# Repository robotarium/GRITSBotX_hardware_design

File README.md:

# GRITSBotX_hardware_design
Documentation relative to the GritsbotX robot circuit board, chassis, and assembly instructions.

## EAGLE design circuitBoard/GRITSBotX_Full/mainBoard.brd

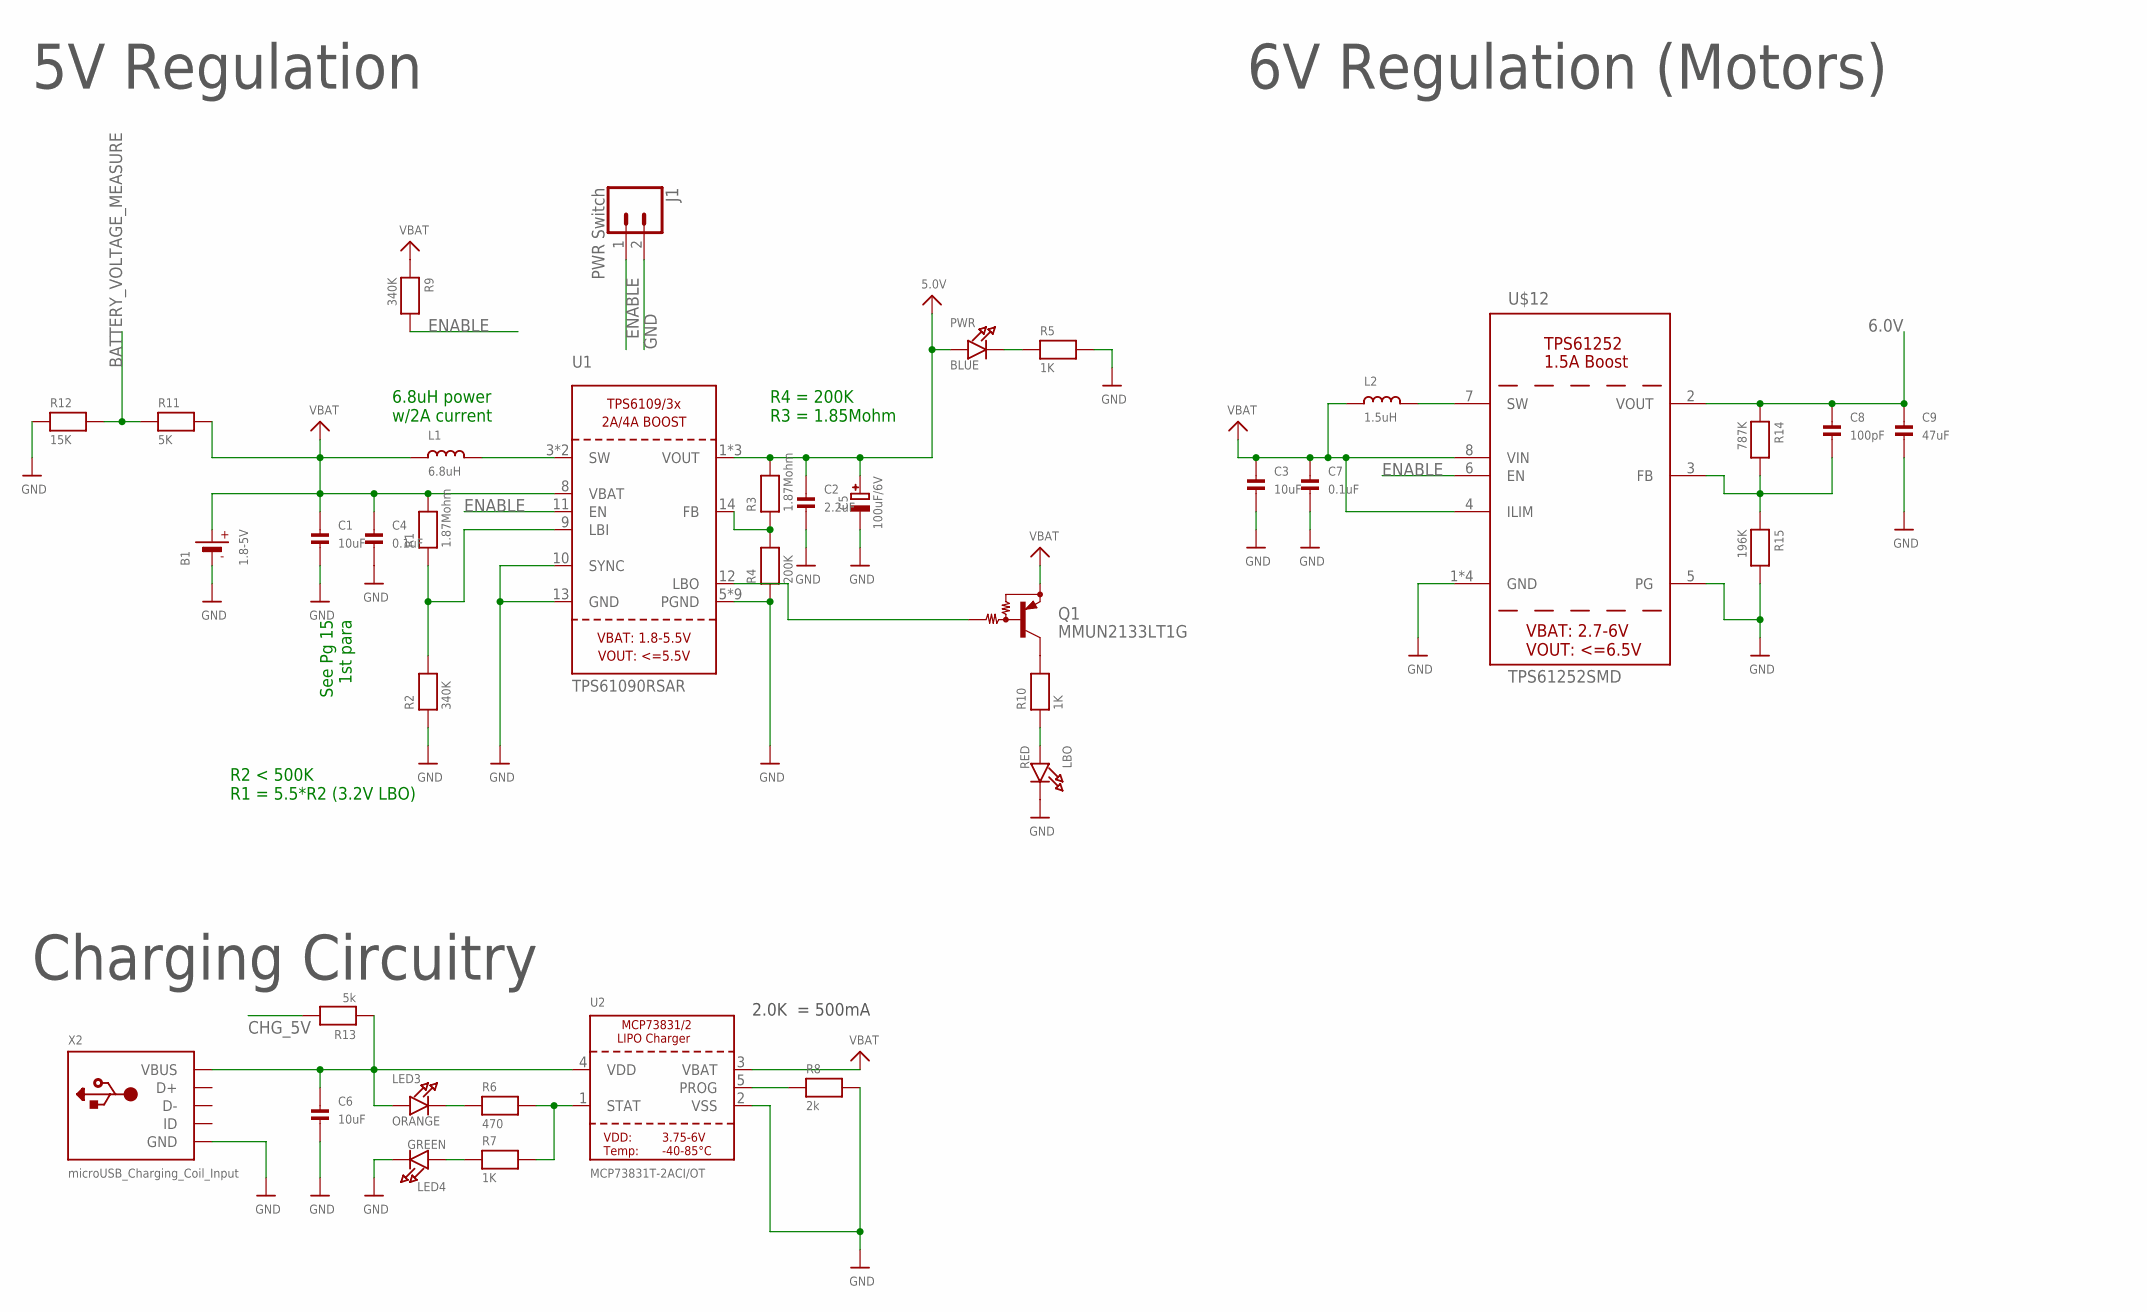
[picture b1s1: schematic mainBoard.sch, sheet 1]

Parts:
B1: 1.8-5V; JSTPH2
C1, C3, C6: 10uF; 0603
C2: 2.2uF; 0603
C4, C7: 0.1uF; 0805
C5: 100uF/6V; EIA3528-21/B-R
C8: 100pF; 0603
C9: 47uF; 1206
J1: PWR Switch; 1X02
L1: 6.8uH; VISHAY_IHLP2525CZER6R8M01
L2: 1.5uH; MURATA_DFE252012P-1R5M=P2
LBO: RED; CHIPLED_0805_NOOUTLINE
LED3: ORANGE; CHIPLED_0805_NOOUTLINE
LED4: GREEN; CHIPLED_0805_NOOUTLINE
PWR: BLUE; CHIPLED_0805_NOOUTLINE
Q1: MMUN2133LT1G; SC59-BEC
R1, R3: 1.87Mohm; 0805
R2, R9: 340K; 0805
R4: 200K; 0805
R5, R7, R10: 1K; 0805
R6: 470; 0805
R8: 2k; 0805
R11: 5K; 0805
R12: 15K; 0805
R13: 5k; 0805
R14: 787K; 0805
R15: 196K; 0805
U1: TPS61090RSAR; PVQFN-16
U2: MCP73831T-2ACI/OT; SOT23-5
U$12: TPS61252SMD; TPS61252
X2: microUSB_Charging_Coil_Input; 4UCONN_20329

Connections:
5.0V: C2.1, C5.+, PWR.A, R3.2, U1.1 (VOUT), U1.15 (VOUT), U1.16 (VOUT); also elsewhere on the board
6.0V: C8.1, C9.1, R14.1, U$12.2 (VOUT); also elsewhere on the board
BATTERY_VOLTAGE_MEASURE: R11.1, R12.2; also elsewhere on the board
CHARGING_BOOL_5V: C6.1, LED3.A, R13.1, U2.4 (VDD), X2.VBUS
CHG_5V: R13.2; also elsewhere on the board
ENABLE: J1.1, R9.2, U1.11 (EN), U$12.6 (EN)
GND: B1.1 (-), C1.2, C2.2, C3.2, C4.2, C5.-, C6.2, C7.2, C9.2, J1.2, LBO.C, LED4.C, R2.1, R4.1, R5.2, R8.2, R12.1, R15.2, U1.5 (PGND), U1.6 (PGND), U1.7 (PGND), U1.10 (SYNC), U1.13 (GND), U1.P$18 (PGND), U1.P$19 (PGND), U1.P$20 (PGND), U1.P$21 (PGND), U1.P$22 (PGND), U1.THERMAL (PGND), U2.2 (VSS), U$12.1 (GND), U$12.5 (PG), U$12.P$2_GND (GND), U$12.P$3_GND (GND), U$12.THERMAL_GND (GND), X2.BASE@1 (GND), X2.BASE@2 (GND), X2.GND, X2.SPRT@1 (GND), X2.SPRT@2 (GND), X2.SPRT@3 (GND), X2.SPRT@4 (GND); also elsewhere on the board
LBO: Q1.B, U1.12 (LBO)
unnamed: L1.P$2 (2), U1.3 (SW), U1.4 (SW)
unnamed: LBO.A, R10.1
unnamed: R1.1, R2.2, U1.9 (LBI)
unnamed: PWR.C, R5.1
unnamed: R3.1, R4.2, U1.14 (FB)
unnamed: LED3.C, R6.1
unnamed: R6.2, R7.2, U2.1 (STAT)
unnamed: R8.1, U2.5 (PROG)
unnamed: LED4.A, R7.1
unnamed: Q1.C, R10.2
unnamed: L2.P$2 (2), U$12.7 (SW)
unnamed: C8.2, R14.2, R15.1, U$12.3 (FB)
VBAT: B1.2 (+), C1.1, C3.1, C4.1, C7.1, L1.P$1 (1), L2.P$1 (1), Q1.E, R1.2, R9.1, R11.2, U1.8 (VBAT), U2.3 (VBAT), U$12.4 (ILIM), U$12.8 (VIN)

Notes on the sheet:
See Pg 15 1st para
6.8uH power w/2A current
R2 < 500K R1 = 5.5*R2 (3.2V LBO)
R4 = 200K R3 = 1.85Mohm
2.0K = 500mA
Charging Circuitry
5V Regulation
6V Regulation (Motors)

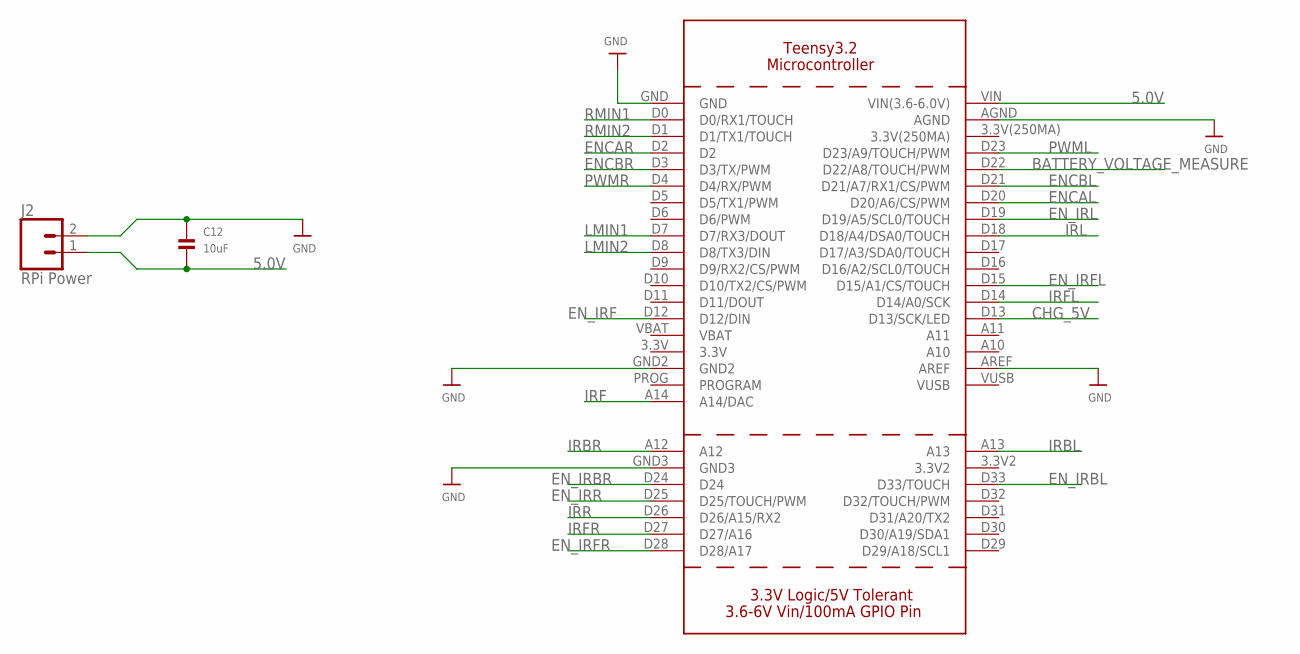
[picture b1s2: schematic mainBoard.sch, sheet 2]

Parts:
C12: 10uF; 0603
J2: RPi Power; 1X02
U$28: TEENSY3_2

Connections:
5.0V: C12.2, J2.1, U$28.VIN (VIN(3.6-6.0V)); also elsewhere on the board
BATTERY_VOLTAGE_MEASURE: U$28.D22 (D22/A8/TOUCH/PWM); also elsewhere on the board
CHG_5V: U$28.D13 (D13/SCK/LED); also elsewhere on the board
ENCAL: U$28.D20 (D20/A6/CS/PWM); also elsewhere on the board
ENCAR: U$28.D2; also elsewhere on the board
ENCBL: U$28.D21 (D21/A7/RX1/CS/PWM); also elsewhere on the board
ENCBR: U$28.D3 (D3/TX/PWM); also elsewhere on the board
EN_IRBL: U$28.D33 (D33/TOUCH); also elsewhere on the board
EN_IRBR: U$28.D24; also elsewhere on the board
EN_IRF: U$28.D12 (D12/DIN); also elsewhere on the board
EN_IRFL: U$28.D15 (D15/A1/CS/TOUCH); also elsewhere on the board
EN_IRFR: U$28.D28 (D28/A17); also elsewhere on the board
EN_IRL: U$28.D19 (D19/A5/SCL0/TOUCH); also elsewhere on the board
EN_IRR: U$28.D25 (D25/TOUCH/PWM); also elsewhere on the board
GND: C12.1, J2.2, U$28.AGND, U$28.AREF, U$28.GND, U$28.GND2, U$28.GND3; also elsewhere on the board
IRBL: U$28.A13; also elsewhere on the board
IRBR: U$28.A12; also elsewhere on the board
IRF: U$28.A14 (A14/DAC); also elsewhere on the board
IRFL: U$28.D14 (D14/A0/SCK); also elsewhere on the board
IRFR: U$28.D27 (D27/A16); also elsewhere on the board
IRL: U$28.D18 (D18/A4/DSA0/TOUCH); also elsewhere on the board
IRR: U$28.D26 (D26/A15/RX2); also elsewhere on the board
LMIN1: U$28.D7 (D7/RX3/DOUT); also elsewhere on the board
LMIN2: U$28.D8 (D8/TX3/DIN); also elsewhere on the board
PWML: U$28.D23 (D23/A9/TOUCH/PWM); also elsewhere on the board
PWMR: U$28.D4 (D4/RX/PWM); also elsewhere on the board
RMIN1: U$28.D0 (D0/RX1/TOUCH); also elsewhere on the board
RMIN2: U$28.D1 (D1/TX1/TOUCH); also elsewhere on the board

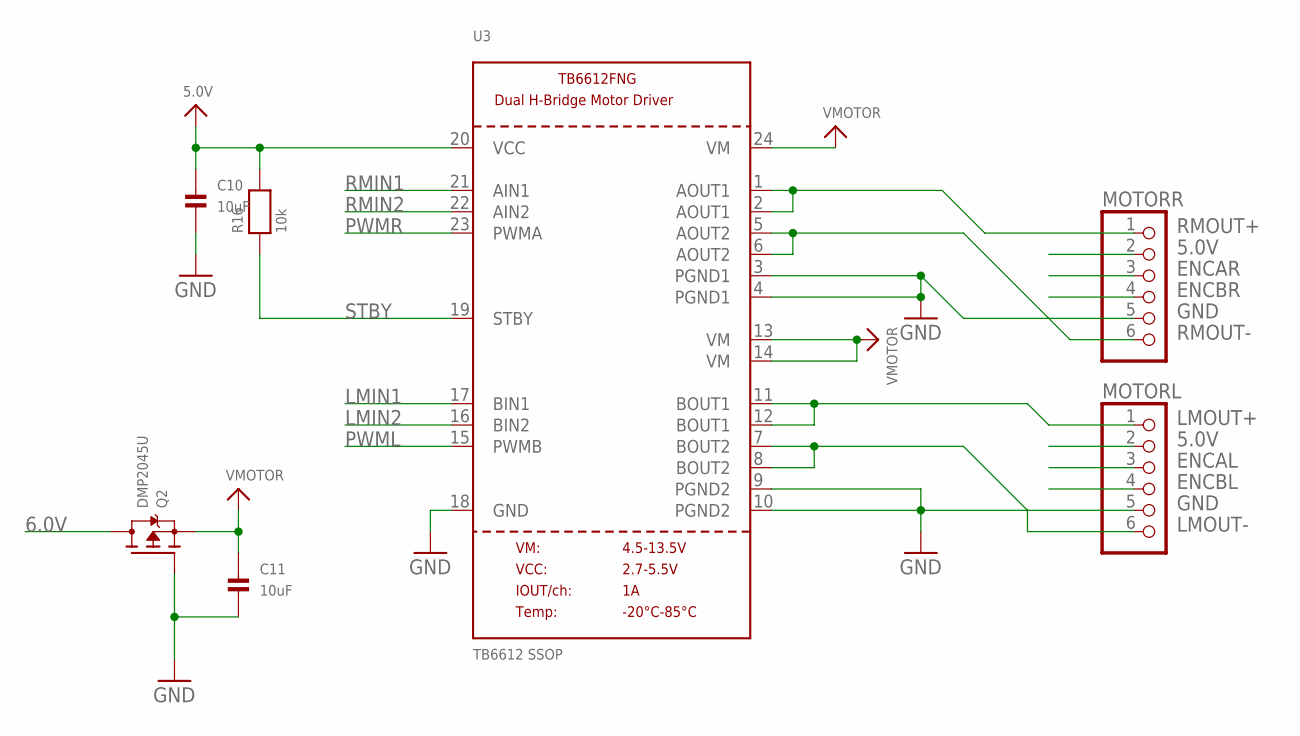
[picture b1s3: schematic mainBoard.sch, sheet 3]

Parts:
C10, C11: 10uF; 0603
MOTORL: PINHD-1X6CB; 1X06-CLEANBIG
MOTORR: PINHD-1X6CB; 1X06-CLEANBIG
Q2: DMP2045U; SOT23-WIDE
R16: 10k; 0805
U3: TB6612 SSOP; SSOP24

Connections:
5.0V: C10.1, MOTORL.2, MOTORR.2, R16.2, U3.20 (VCC); also elsewhere on the board
6.0V: Q2.3 (D); also elsewhere on the board
ENCAL: MOTORL.3; also elsewhere on the board
ENCAR: MOTORR.3; also elsewhere on the board
ENCBL: MOTORL.4; also elsewhere on the board
ENCBR: MOTORR.4; also elsewhere on the board
GND: C10.2, C11.2, MOTORL.5, MOTORR.5, Q2.1 (G), U3.3 (PGND1), U3.4 (PGND1), U3.9 (PGND2), U3.10 (PGND2), U3.18 (GND); also elsewhere on the board
LMIN1: U3.17 (BIN1); also elsewhere on the board
LMIN2: U3.16 (BIN2); also elsewhere on the board
LMOUT+: MOTORL.1, U3.11 (BOUT1), U3.12 (BOUT1)
LMOUT-: MOTORL.6, U3.7 (BOUT2), U3.8 (BOUT2)
PWML: U3.15 (PWMB); also elsewhere on the board
PWMR: U3.23 (PWMA); also elsewhere on the board
RMIN1: U3.21 (AIN1); also elsewhere on the board
RMIN2: U3.22 (AIN2); also elsewhere on the board
RMOUT+: MOTORR.1, U3.1 (AOUT1), U3.2 (AOUT1)
RMOUT-: MOTORR.6, U3.5 (AOUT2), U3.6 (AOUT2)
STBY: R16.1, U3.19 (STBY)
VMOTOR: C11.1, Q2.2 (S), U3.13 (VM), U3.14 (VM), U3.24 (VM)

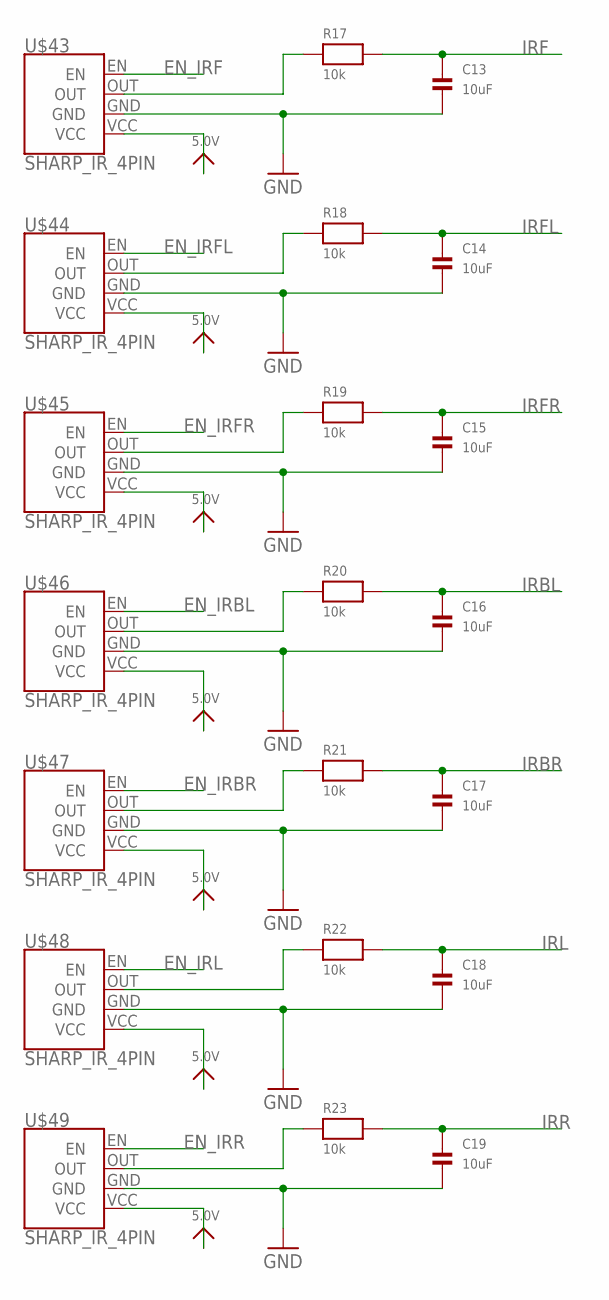
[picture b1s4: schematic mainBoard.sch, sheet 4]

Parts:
C13, C14, C15, C16, C17, C18, C19: 10uF; 0603
R17, R18, R19, R20, R21, R22, R23: 10k; 0805
U$43, U$44, U$45, U$46, U$47, U$48, U$49: SHARP_IR_4PIN

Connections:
5.0V: U$43.VCC, U$44.VCC, U$45.VCC, U$46.VCC, U$47.VCC, U$48.VCC, U$49.VCC; also elsewhere on the board
EN_IRBL: U$46.EN; also elsewhere on the board
EN_IRBR: U$47.EN; also elsewhere on the board
EN_IRF: U$43.EN; also elsewhere on the board
EN_IRFL: U$44.EN; also elsewhere on the board
EN_IRFR: U$45.EN; also elsewhere on the board
EN_IRL: U$48.EN; also elsewhere on the board
EN_IRR: U$49.EN; also elsewhere on the board
GND: C13.2, C14.2, C15.2, C16.2, C17.2, C18.2, C19.2, U$43.GND, U$44.GND, U$45.GND, U$46.GND, U$47.GND, U$48.GND, U$49.GND; also elsewhere on the board
IRBL: C16.1, R20.2; also elsewhere on the board
IRBR: C17.1, R21.2; also elsewhere on the board
IRF: C13.1, R17.2; also elsewhere on the board
IRFL: C14.1, R18.2; also elsewhere on the board
IRFR: C15.1, R19.2; also elsewhere on the board
IRL: C18.1, R22.2; also elsewhere on the board
IRR: C19.1, R23.2; also elsewhere on the board
unnamed: R23.1, U$49.OUT
unnamed: R22.1, U$48.OUT
unnamed: R21.1, U$47.OUT
unnamed: R20.1, U$46.OUT
unnamed: R19.1, U$45.OUT
unnamed: R18.1, U$44.OUT
unnamed: R17.1, U$43.OUT

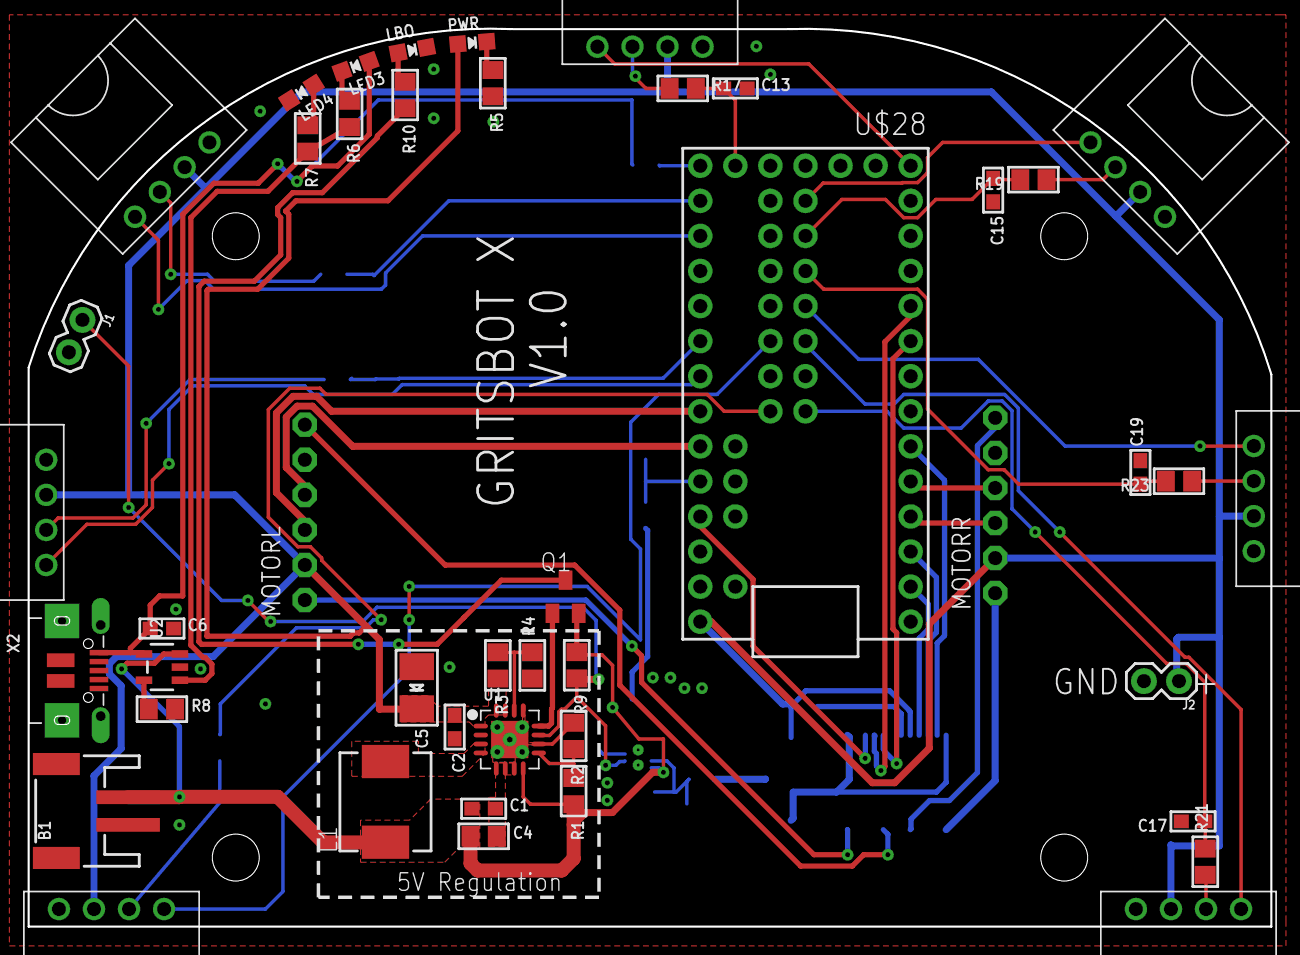
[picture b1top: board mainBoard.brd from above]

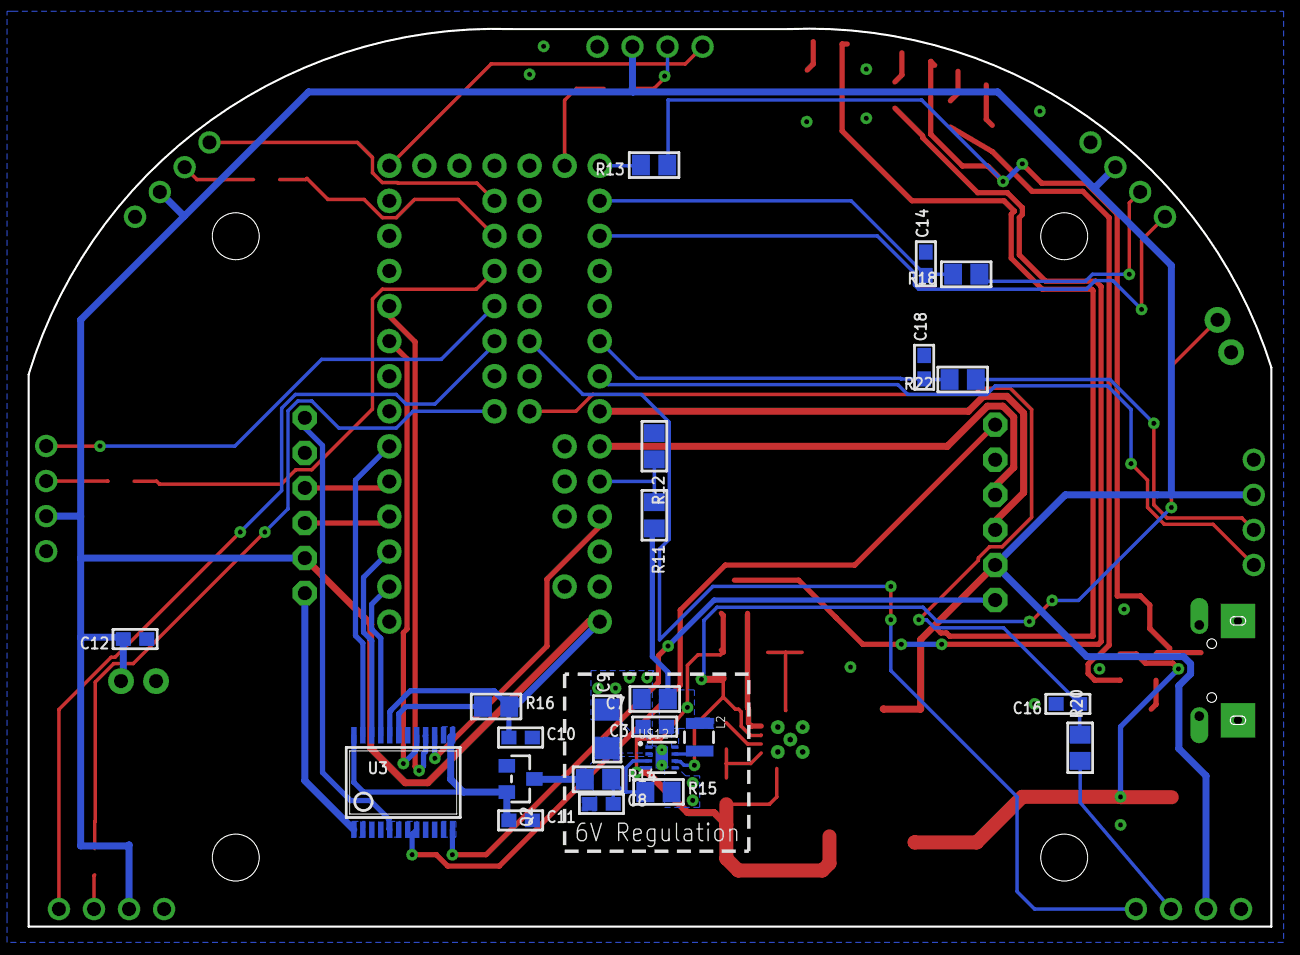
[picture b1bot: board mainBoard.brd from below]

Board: 2 copper layers, 90.0 x 65.0 mm, 72 parts (23 on the bottom side), 58 nets.

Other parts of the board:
U$1, U$2, U$3, U$4: M3_SCREW

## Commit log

2020-12-18 Adding material

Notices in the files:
parts and their libraries:
SparkFun-Aesthetics: Licensing: Creative Commons ShareAlike 4.0 International - https://creativecommons.org/licenses/by-sa/4.0
microbuilder: This work is placed in the public domain, and may be freely used for commercial and non-commercial work with the following conditions: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
